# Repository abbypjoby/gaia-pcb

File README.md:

# gaia-pcb

### Software Used
Kicad - opensource
https://www.kicad-pcb.org/

### Tutorial
1. Kicad Introduction - https://www.youtube.com/watch?v=vaCVh2SAZY4
2. Kicad Create Custom Symbol - https://www.youtube.com/watch?v=c2niS9ZRBHo
3. https://www.youtube.com/watch?v=4Gtd7xY6zS4&t=3s

The complete series - https://www.youtube.com/watch?v=c2niS9ZRBHo&list=RDCMUCclJCqMDAkyVGsm5oFOTXIQ&start_radio=1

## Creating a New Component
- tools 
- symbol library editor 
- file create new Library 
- create new component (button) 
- select required newly created library (new component is added here) 
- give new component name 
- save it, now create the symbol 
- click pin button, add all the pins with proper name and numbers

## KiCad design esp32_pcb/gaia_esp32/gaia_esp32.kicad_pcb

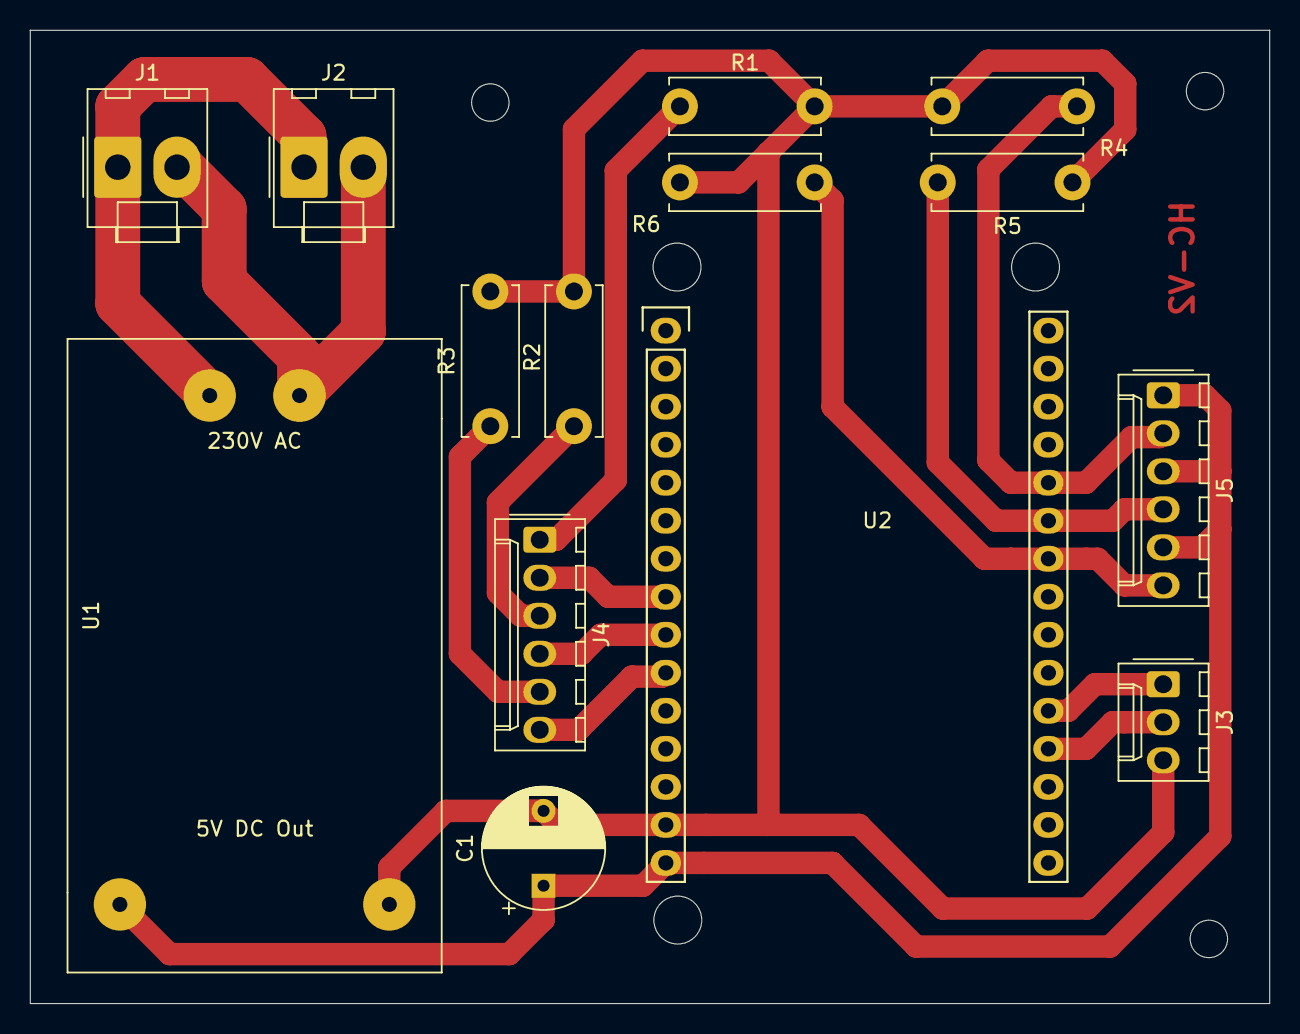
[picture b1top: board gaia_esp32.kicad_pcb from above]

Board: 2 copper layers, 82.8 x 65.0 mm, 17 parts (0 on the bottom side), 15 nets.

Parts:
 : H; MountingHole_2.5mm
 #2,  #3: H; MountingHole_2.5mm
C1: CP1; CP_Radial_D8.0mm_P5.00mm
J1: supply; Molex_KK-396_A-41791-0002_1x02_P3.96mm_Vertical
J2: motor; Molex_KK-396_A-41791-0002_1x02_P3.96mm_Vertical
J3: Conn_01x03; Molex_KK-254_AE-6410-03A_1x03_P2.54mm_Vertical
J4: LED_ARRAY; Molex_KK-254_AE-6410-06A_1x06_P2.54mm_Vertical
J5: SWITCH_ARRAY; Molex_KK-254_AE-6410-06A_1x06_P2.54mm_Vertical
R1, R2, R3: 330E; resistor
R4, R5, R6: 10K; resistor
U1: pcb_power_supply_Vcc_one_supply; 230_5V_supply_HiLink
U2: NodeMCU

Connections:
+5V: C1.1, J5.1, J5.3, J5.5, U1.3, U2.15
GND: C1.2, J3.3, R1.2, R2.2, R3.2, R4.1, R5.1, R6.1, U1.4, U2.14
unnamed: J1.1, J2.1, U1.2
unnamed: J1.2, J2.2, U1.1
unnamed: J3.1, U2.20
unnamed: J3.2, U2.19
unnamed: J4.1, R1.1
unnamed: J4.2, U2.8
unnamed: J4.3, R2.1
unnamed: J4.4, U2.9
unnamed: J4.5, R3.1
unnamed: J4.6, U2.10
unnamed: J5.2, R4.2, U2.26
unnamed: J5.4, R5.2, U2.25
unnamed: J5.6, R6.2, U2.24

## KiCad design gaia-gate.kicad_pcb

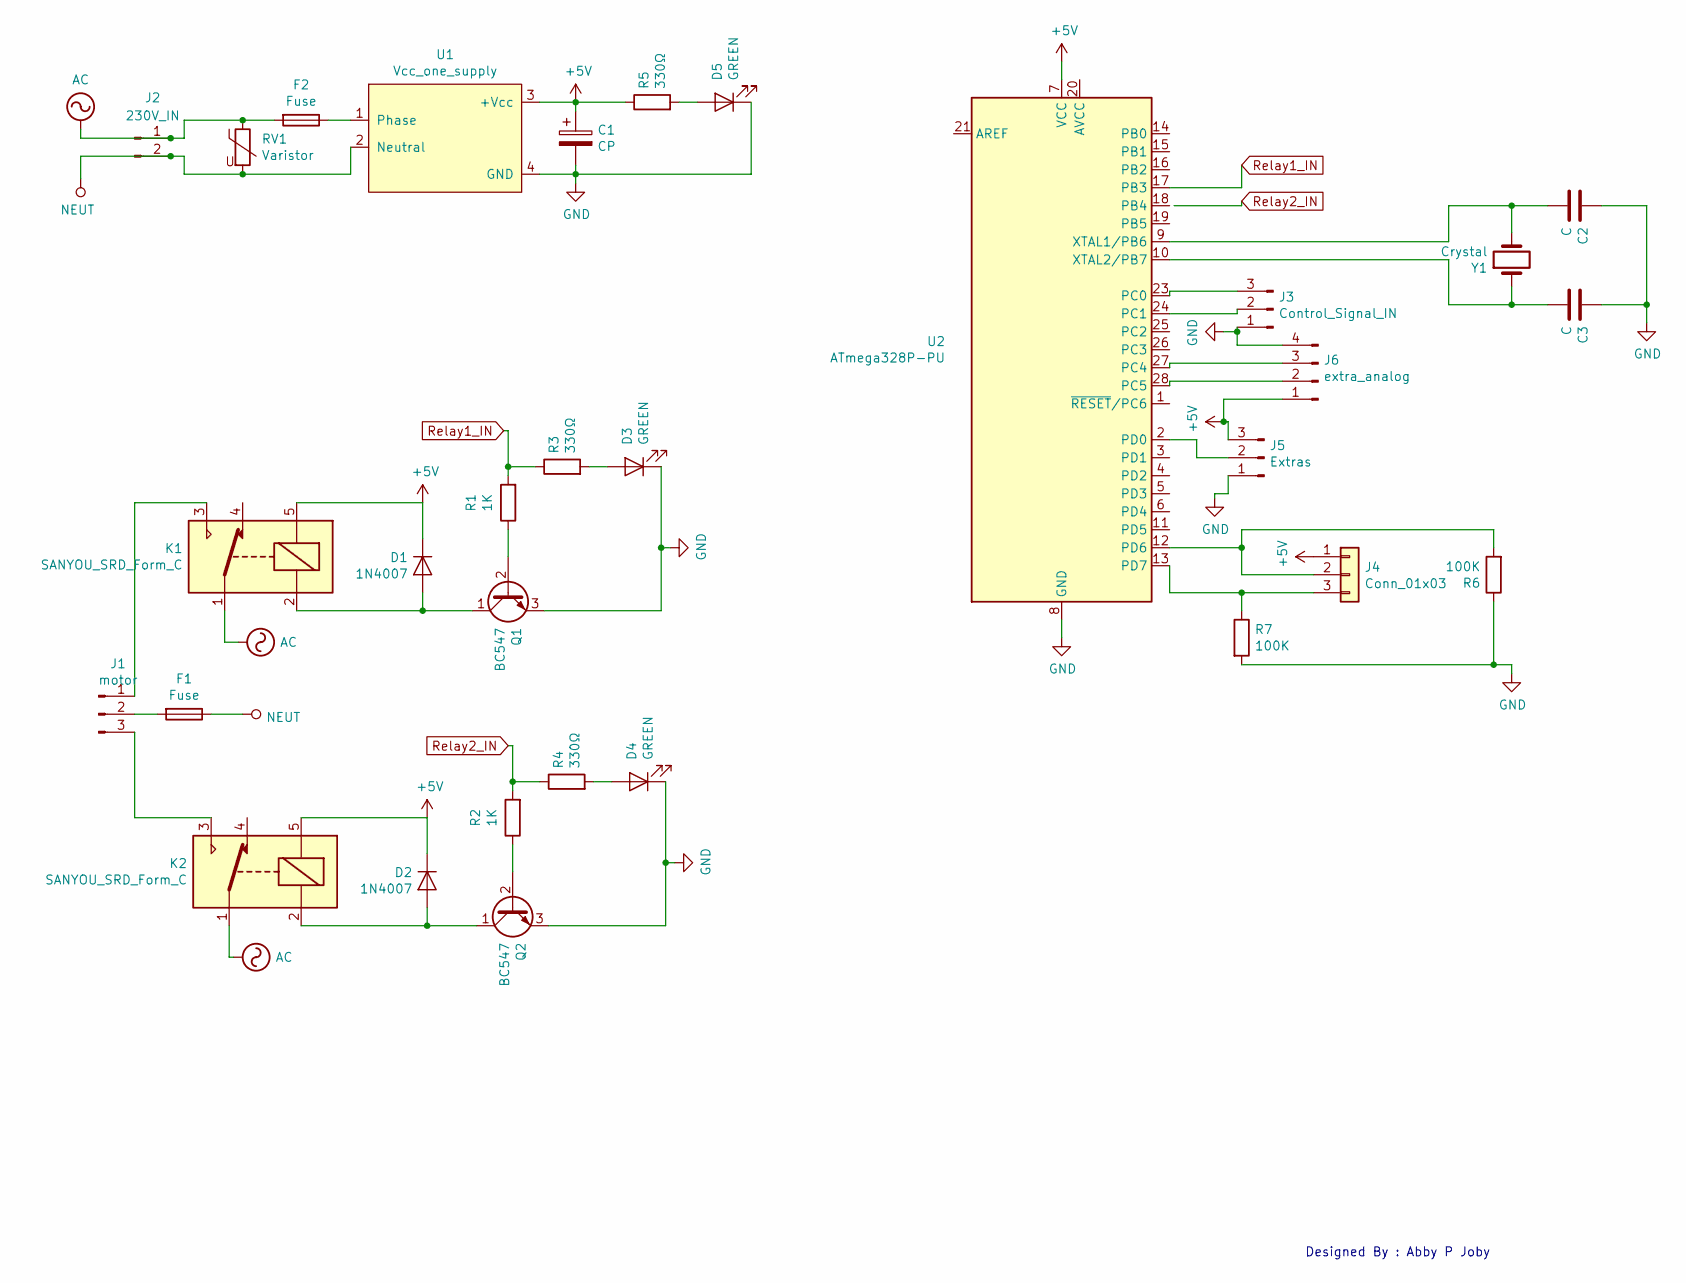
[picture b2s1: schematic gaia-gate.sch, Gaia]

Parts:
C1: CP; CP_Radial_D8.0mm_P5.00mm
C2, C3: C; C_Disc_D3.8mm_W2.6mm_P2.50mm
D1, D2: 1N4007; D_DO-41_SOD81_P10.16mm_Horizontal
D3, D4, D5: GREEN; LED_D5.0mm
F1, F2: Fuse
J1: motor; Molex_KK-396_A-41791-0003_1x03_P3.96mm_Vertical
J2: 230V_IN; Molex_KK-396_A-41791-0002_1x02_P3.96mm_Vertical
J3: Control_Signal_IN; Molex_KK-396_A-41791-0003_1x03_P3.96mm_Vertical
J4: Conn_01x03; Molex_KK-396_A-41791-0003_1x03_P3.96mm_Vertical
J5: Extras; Molex_KK-396_A-41791-0003_1x03_P3.96mm_Vertical
J6: extra_analog; Molex_KK-396_A-41791-0004_1x04_P3.96mm_Vertical
K1, K2: SANYOU_SRD_Form_C; Relay_SPDT_SANYOU_SRD_Series_Form_C
Q1, Q2: BC547; TO-92_Inline_Wide
R1, R2: 1K; resistor
R3, R4, R5: 330Ω; resistor
R6, R7: 100K; resistor
RV1: Varistor; RV_Disc_D9mm_W6.1mm_P5mm
U1: Vcc_one_supply; 230_5V_supply_HiLink
U2: ATmega328P-PU; DIP-28_W7.62mm_Socket_LongPads
Y1: Crystal; Crystal_HC18-U_Vertical

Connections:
+5V: C1.1, D1.1 (K), D2.1 (K), J4.1, J5.3, J6.1, K1.5, K2.5, R5.1, U1.3 (+Vcc), U2.7 (VCC)
AC: F2.2, J2.1, K1.1, K2.1, RV1.1
GND: C1.2, C2.1, C3.1, D3.1 (K), D4.1 (K), D5.1 (K), J3.1, J5.1, J6.4, Q1.3 (E), Q2.3 (E), R6.1, R7.2, U1.4 (GND), U2.8 (GND), U2.22 (GND)
NEUT: F1.1, J2.2, RV1.2, U1.2 (Neutral)
unnamed: C2.2, U2.9 (XTAL1/PB6), Y1.2
unnamed: C3.2, U2.10 (XTAL2/PB7), Y1.1
unnamed: D1.2 (A), K1.2, Q1.1 (C)
unnamed: D2.2 (A), K2.2, Q2.1 (C)
unnamed: D3.2 (A), R3.2
unnamed: D4.2 (A), R4.2
unnamed: D5.2 (A), R5.2
unnamed: F1.2, J1.2
unnamed: F2.1, U1.1 (Phase)
unnamed: J1.1, K1.3
unnamed: J1.3, K2.3
unnamed: J3.2, U2.24 (PC1)
unnamed: J3.3, U2.23 (PC0)
unnamed: J4.2, R6.2, U2.12 (PD6)
unnamed: J4.3, R7.1, U2.13 (PD7)
unnamed: J5.2, U2.2 (PD0)
unnamed: J6.2, U2.28 (PC5)
unnamed: J6.3, U2.27 (PC4)
unnamed: Q1.2 (B), R1.1
unnamed: Q2.2 (B), R2.1
Relay1_IN: R1.2, R3.1, U2.17 (PB3); also elsewhere on the board
Relay2_IN: R2.2, R4.1

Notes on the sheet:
Designed By : Abby P Joby

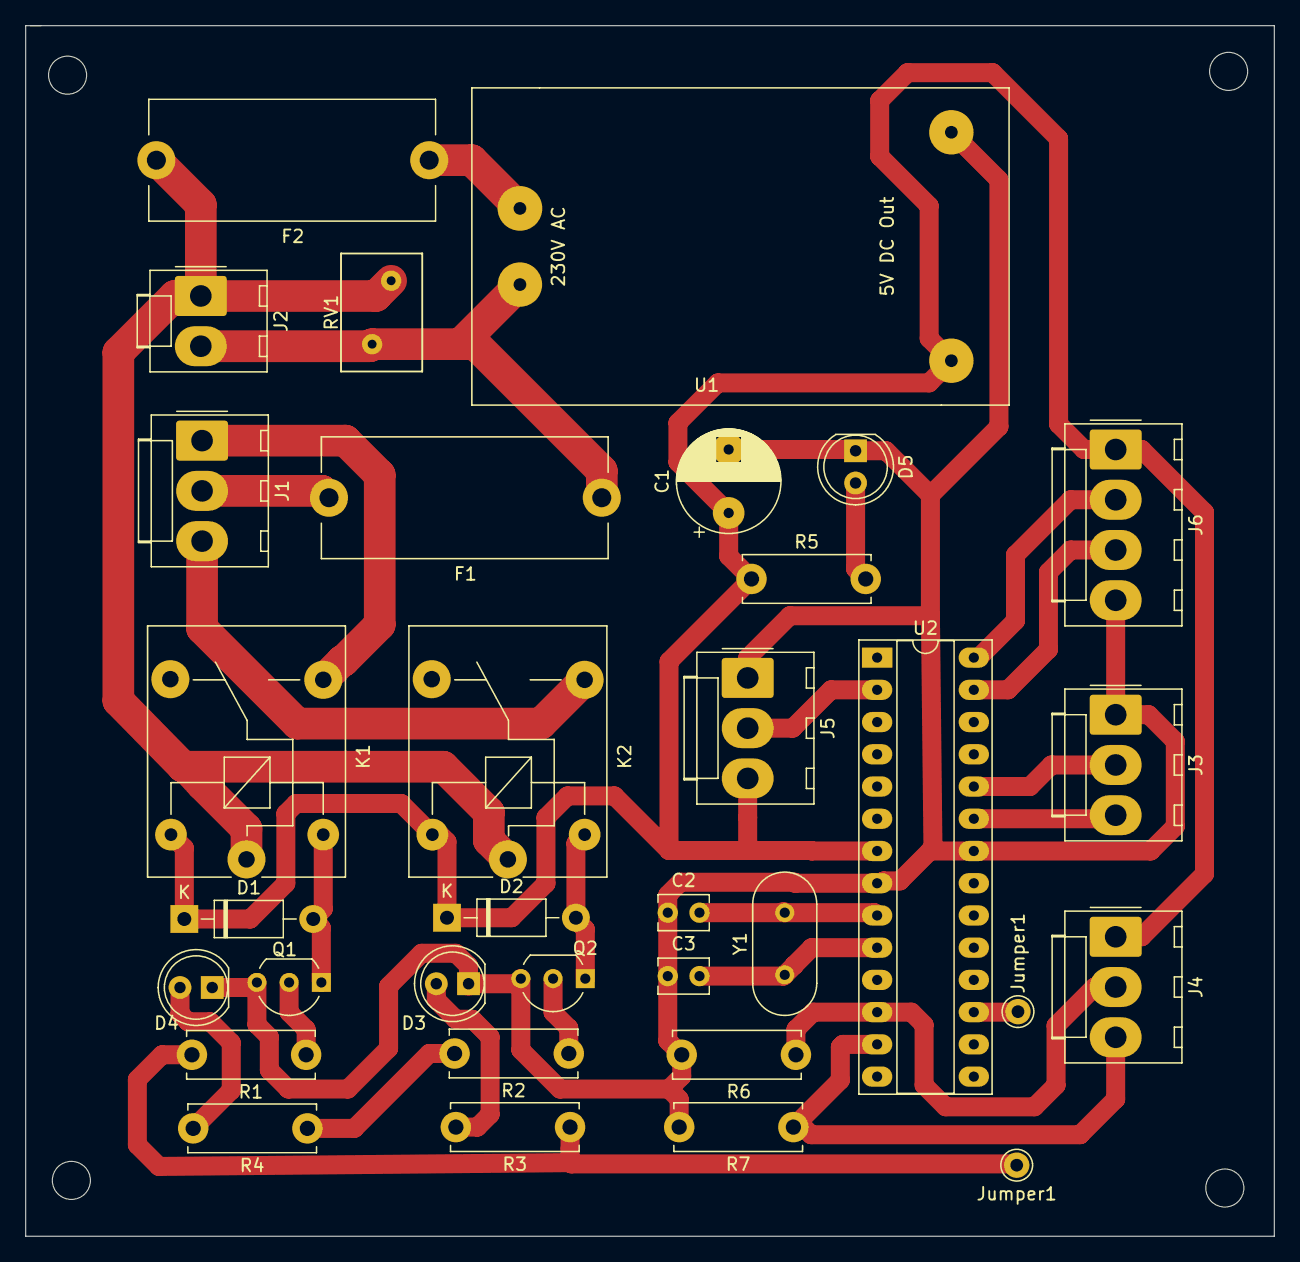
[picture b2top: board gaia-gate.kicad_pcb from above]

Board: 2 copper layers, 98.4 x 95.4 mm, 37 parts (0 on the bottom side), 26 nets.

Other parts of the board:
 : MountingHole_3mm
 #2,  #3,  #4: MountingHole_3mm
Jumper1, Jumper1#2: Pin_D1.0mm_L10.0mm

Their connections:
Relay1_IN: Jumper1.1, Jumper1#2.1; also elsewhere on the board

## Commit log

2020-05-07 kicad circuit v1
2020-05-14 v2 withcontrol board circuit
2020-06-14 working PCB v2
2021-06-26 latest pcb
